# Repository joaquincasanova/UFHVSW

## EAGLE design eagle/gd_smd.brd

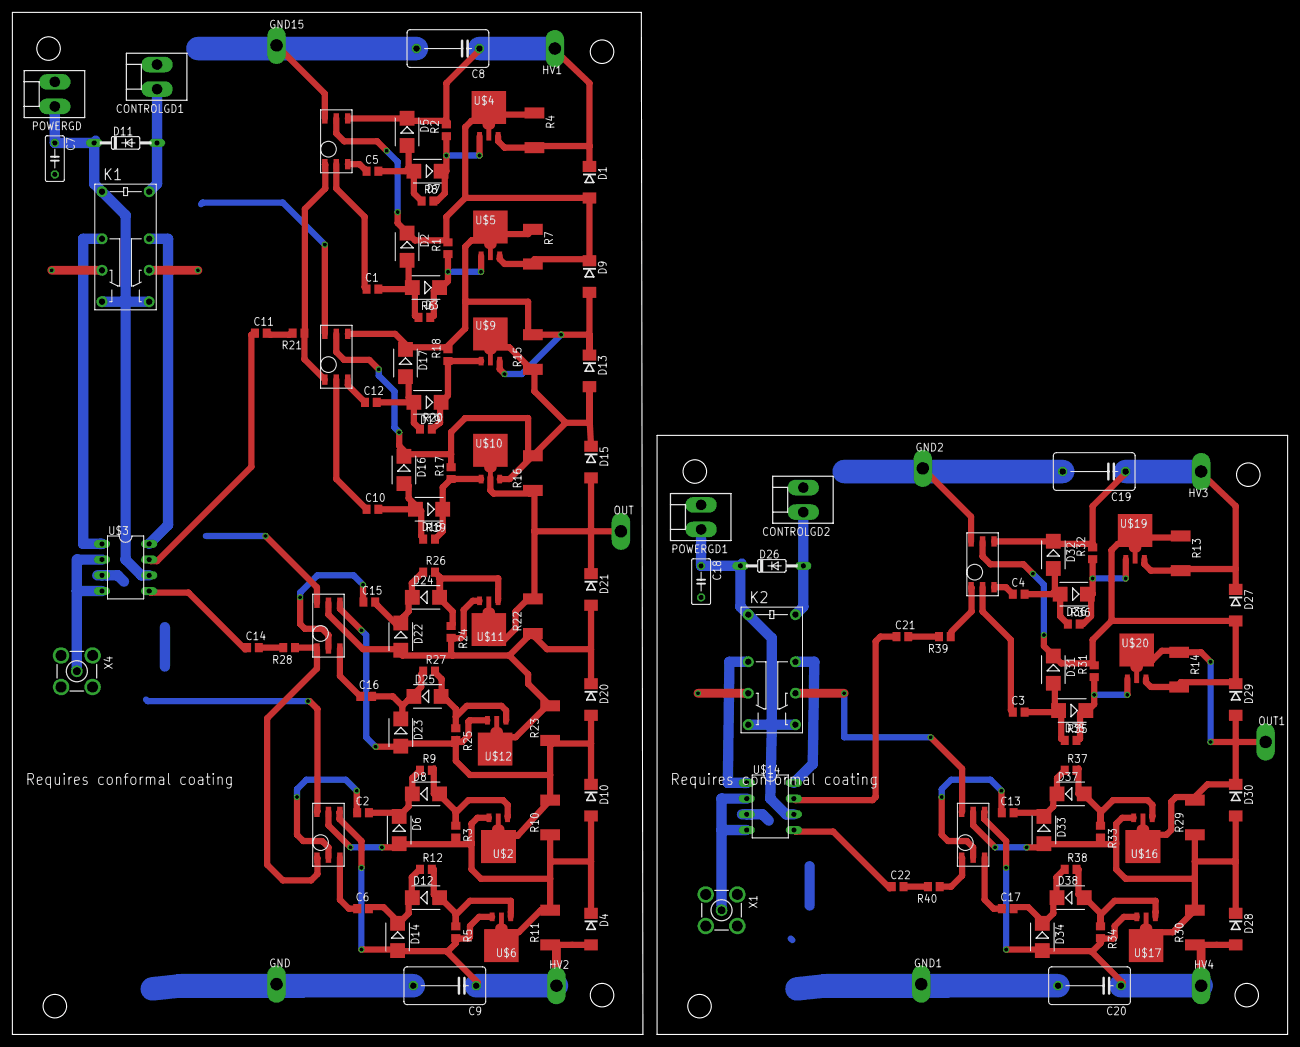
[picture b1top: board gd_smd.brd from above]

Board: 2 copper layers, 206.0 x 165.1 mm, 138 parts (0 on the bottom side), 74 nets.

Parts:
C1, C2, C3, C4, C5, C6, C10, C11, C12, C13, C14, C15, C16, C17, C21, C22: 1u; C0805
C7, C18: 10n; C050-030X075
C8, C9, C19, C20: 10p; C102-064X133
CONTROLGD1, CONTROLGD2: KK-156-2
D1, D4, D9, D10, D13, D15, D20, D21, D27, D28, D29, D30: SMBJ170D-M3/H; DO214AA
D2, D5, D6, D14, D16, D17, D22, D23, D31, D32, D33, D34: 1SMB5918BT3G; SMB
D3, D7, D8, D12, D18, D19, D24, D25, D35, D36, D37, D38: SMB
D11, D26: 1N4148DO35-10; DO35-10
GND, GND1, GND2, GND15: TPPAD1-20Y; P1-20Y
HV1, HV2, HV3, HV4: TPPAD1-20Y; P1-20Y
K1, K2: G5V-2
OUT, OUT1: TPPAD1-20Y; P1-20Y
POWERGD, POWERGD1: KK-156-2
R1, R2, R3, R5, R17, R18, R24, R25, R31, R32, R33, R34: 100k; R0805
R4, R7, R10, R11, R13, R14, R15, R16, R22, R23, R29, R30: 10M; R2512
R6, R8, R9, R12, R19, R20, R21, R26, R27, R28, R35, R36, R37, R38, R39, R40: 10; R0805
U$1, U$7, U$8, U$13, U$15, U$18: DA-2320SMD6; SMD6
U$2, U$6, U$11, U$12, U$16, U$17: VN2450; SOT89-BCE
U$3, U$14: UCC27425; DIL08
U$4, U$5, U$9, U$10, U$19, U$20: VP2450; SOT89-BCE
X1, X4: BU-SMA-V

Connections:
+15V: C7.1, D11.C, K1.1, K1.8, K1.9, POWERGD.1, U$3.6
+15V1: C18.1, D26.C, K2.1, K2.8, K2.9, POWERGD1.1, U$14.6
ENSW: CONTROLGD1.1, D11.A, K1.16
ENSW1: CONTROLGD2.1, D26.A, K2.16
GND: C7.2, C8.2, C9.2, CONTROLGD1.2, GND.TP, GND15.TP, K1.6, K1.11, POWERGD.2, U$1.P$6, U$3.3, U$7.P$6, U$8.P$6, U$13.P$6, X4.2, X4.3, X4.4, X4.5
GND1: C18.2, C19.2, C20.2, CONTROLGD2.2, GND1.TP, GND2.TP, K2.6, K2.11, POWERGD1.2, U$14.3, U$15.P$6, U$18.P$6, X1.2, X1.3, X1.4, X1.5
unnamed: U$3.2, U$3.4, X4.1
unnamed: C11.1, U$3.7
unnamed: U$14.2, U$14.4, X1.1
unnamed: C14.1, U$3.5
unnamed: C1.1, U$1.P$2
unnamed: C21.1, U$14.7
unnamed: C5.1, U$1.P$3
unnamed: D3.C, R1.1, R6.2, U$5.B
unnamed: C22.1, U$14.5
unnamed: C1.2, D2.A, D3.A, R6.1
unnamed: D12.A, R5.1, R12.2, U$6.B
unnamed: D7.C, R2.1, R8.2, U$4.B
unnamed: D4.C, D6.A, D10.A, R3.2, R10.1, R11.2, U$2.E, U$6.C, U$6.C@1, U$7.P$5
unnamed: K1.4, U$3.1
unnamed: K1.13, U$3.8
unnamed: C5.2, D5.A, D7.A, R8.1
unnamed: C8.1, D1.C, D5.C, HV1.TP, R2.2, R4.2, U$1.P$4, U$4.E
unnamed: D1.A, D2.C, D9.C, R1.2, R4.1, R7.2, U$1.P$5, U$4.C, U$4.C@1, U$5.E
unnamed: K2.4, U$14.1
unnamed: K2.13, U$14.8
unnamed: C3.1, U$15.P$2
unnamed: C2.1, U$7.P$2
unnamed: C6.1, U$7.P$3
unnamed: C9.1, D4.A, D14.A, HV2.TP, R5.2, R11.1, U$6.E, U$7.P$4
unnamed: C2.2, D6.C, D8.C, R9.1
unnamed: D15.A, D21.C, OUT.TP, R16.1, R22.2, U$10.C, U$10.C@1, U$11.C, U$11.C@1
unnamed: C6.2, D12.C, D14.C, R12.1
unnamed: C10.1, U$8.P$2
unnamed: C12.1, U$8.P$3
unnamed: C12.2, D17.A, D19.A, R20.1
unnamed: C4.1, U$15.P$3
unnamed: D9.A, D13.C, D17.C, R7.1, R15.2, R18.2, U$5.C, U$5.C@1, U$8.P$4, U$9.E
unnamed: D13.A, D15.C, D16.C, R15.1, R16.2, R17.2, U$8.P$5, U$9.C, U$9.C@1, U$10.E
unnamed: D18.C, R17.1, R19.2, U$10.B
unnamed: C10.2, D16.A, D18.A, R19.1
unnamed: D19.C, R18.1, R20.2, U$9.B
unnamed: R21.1, U$1.P$1, U$8.P$1
unnamed: C11.2, R21.2
unnamed: C13.1, U$18.P$2
unnamed: C15.1, U$13.P$2
unnamed: C16.1, U$13.P$3
unnamed: C15.2, D22.C, D24.C, R26.1
unnamed: C16.2, D23.C, D25.C, R27.1
unnamed: C17.1, U$18.P$3
unnamed: C13.2, D33.C, D37.C, R37.1
unnamed: D20.C, D21.A, D22.A, R22.1, R23.2, R24.2, U$11.E, U$12.C, U$12.C@1, U$13.P$5
unnamed: D25.A, R25.1, R27.2, U$12.B
unnamed: R28.1, U$7.P$1, U$13.P$1
unnamed: C14.2, R28.2
unnamed: D24.A, R24.1, R26.2, U$11.B
unnamed: D10.C, D20.A, D23.A, R10.2, R23.1, R25.2, U$2.C, U$2.C@1, U$12.E, U$13.P$4
unnamed: C17.2, D34.C, D38.C, R38.1
unnamed: C4.2, D32.A, D36.A, R36.1
unnamed: C19.1, D27.C, D32.C, HV3.TP, R13.2, R32.2, U$15.P$4, U$19.E
unnamed: D28.C, D30.A, D33.A, R29.1, R30.2, R33.2, U$16.E, U$17.C, U$17.C@1, U$18.P$5
unnamed: D27.A, D29.C, D31.C, R13.1, R14.2, R31.2, U$15.P$5, U$19.C, U$19.C@1, U$20.E
unnamed: D35.C, R31.1, R35.2, U$20.B
unnamed: C3.2, D31.A, D35.A, R35.1
unnamed: D38.A, R34.1, R38.2, U$17.B
unnamed: D36.C, R32.1, R36.2, U$19.B
unnamed: D37.A, R33.1, R37.2, U$16.B
unnamed: C20.1, D28.A, D34.A, HV4.TP, R30.1, R34.2, U$17.E, U$18.P$4
unnamed: R39.1, U$15.P$1
unnamed: C21.2, R39.2
unnamed: R40.1, U$18.P$1
unnamed: C22.2, R40.2
unnamed: D29.A, D30.C, OUT1.TP, R14.1, R29.2, U$16.C, U$16.C@1, U$20.C, U$20.C@1
unnamed: D8.A, R3.1, R9.2, U$2.B

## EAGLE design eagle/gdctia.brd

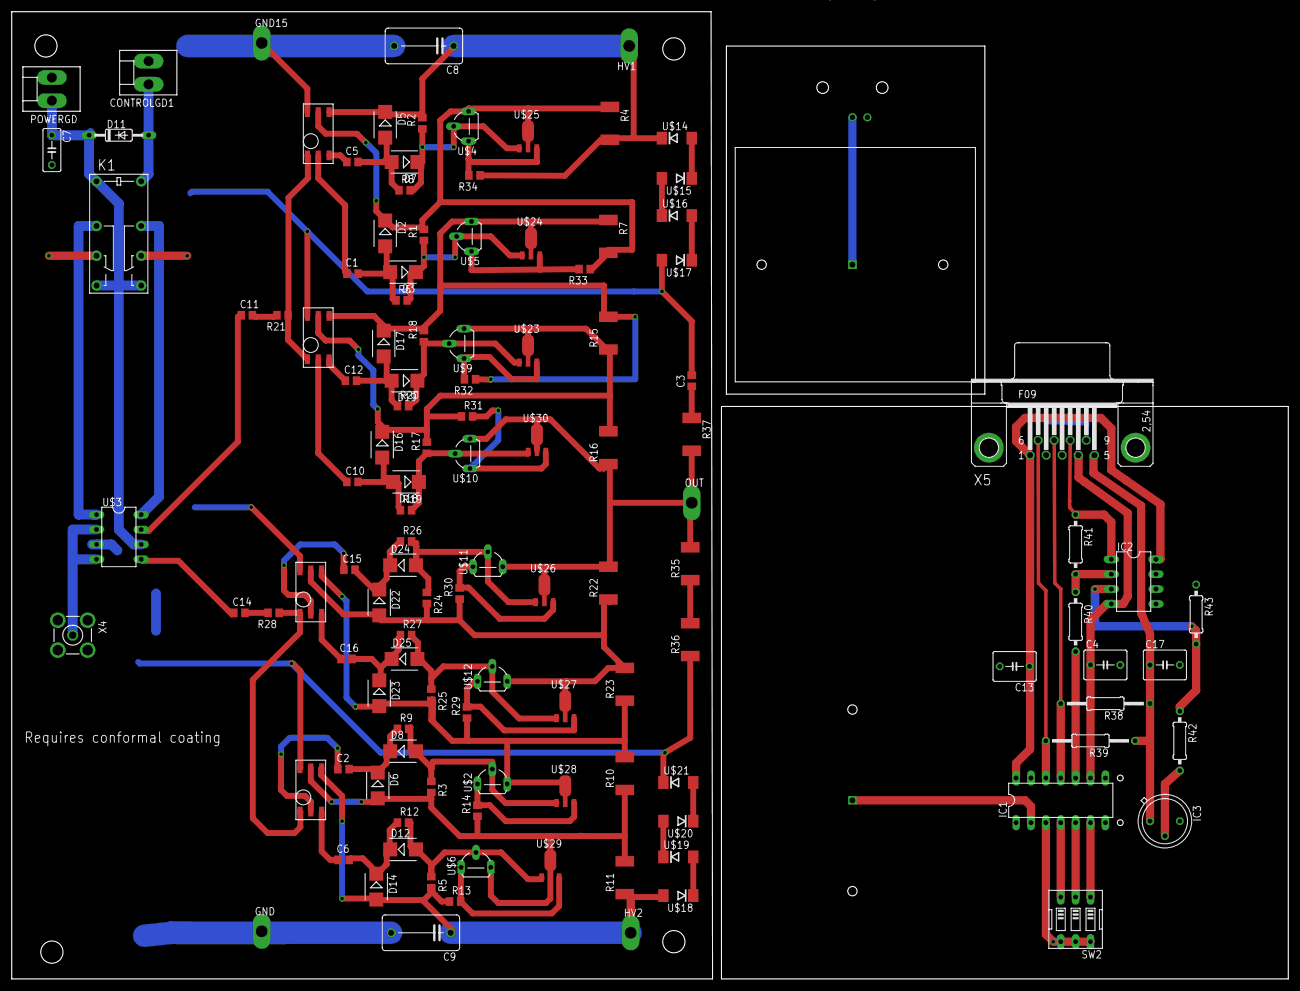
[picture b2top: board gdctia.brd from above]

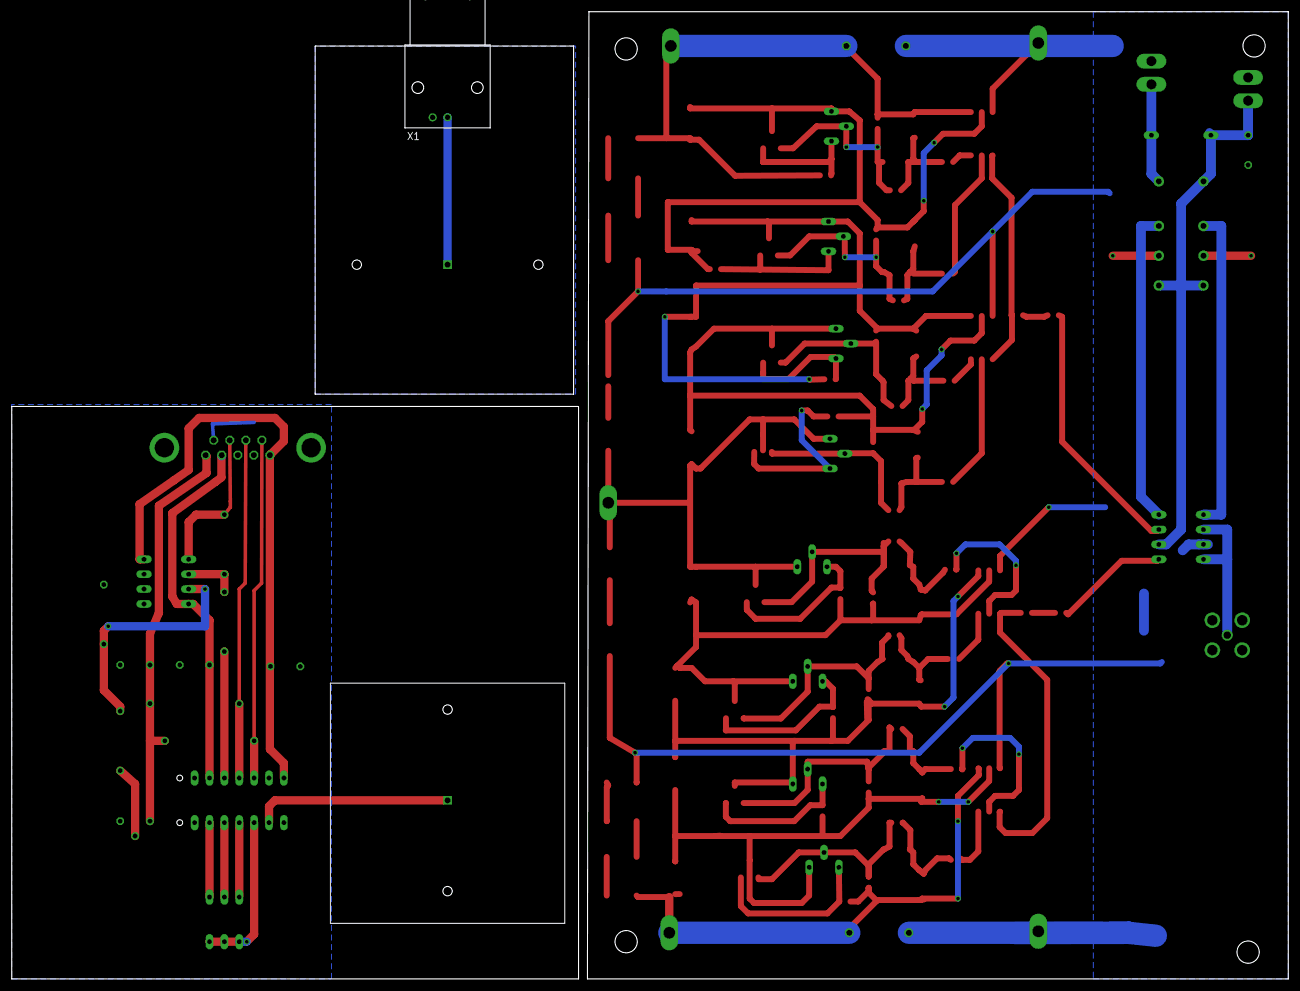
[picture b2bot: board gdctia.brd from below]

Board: 2 copper layers, 217.9 x 165.1 mm, 123 parts (2 on the bottom side), 78 nets.

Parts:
C1, C2, C5, C6, C10, C11, C12, C14, C15, C16: 1u; C0805
C3: 10n; C0805
C4, C13, C17: 10n; C050-050X075
C7: 10n; C050-030X075
C8, C9: 10p; C102-064X133
CONTROLGD1: KK-156-2
D2, D5, D6, D14, D16, D17, D22, D23: 1SMB5918BT3G; SMB
D3, D7, D8, D12, D18, D19, D24, D25: SMB
D11: 1N4148DO35-10; DO35-10
GND, GND15: TPPAD1-20Y; P1-20Y
HV1, HV2: TPPAD1-20Y; P1-20Y
IC1: IVC102UADAPTOR; DIL14
IC2: LT1352PA; DIL08
IC3: AD580H; TO39
K1: G5V-2
OUT: TPPAD1-20Y; P1-20Y
POWERGD: KK-156-2
R1, R2, R3, R5, R17, R18, R24, R25: 100k; R0805
R4, R7, R10, R11, R15, R16, R22, R23, R35, R36, R37: 10M; R2512
R6, R8, R9, R12, R19, R20, R21, R26, R27, R28: 10; R0805
R13, R14, R29, R30: 6.67; R0805
R31, R32, R33, R34: 1.25; R0805
R38, R39: 10k; 0207/15
R40, R43: 10k; 0207/10
R41, R42: 1.5M; 0207/10
SW2: EDG-03
U$1, U$7, U$8, U$13: DA-2320SMD6; SMD6
U$2, U$6, U$11, U$12: VN0550L; TO92L
U$3: UCC27425; DIL08
U$4, U$5, U$9, U$10: VP0550L; TO92L
U$14, U$15, U$16, U$17, U$18, U$19, U$20, U$21: SMBJ170D-M3/H; DO214AA
U$22, U$31: CTIA
U$23, U$24, U$25, U$30: VP2450; SOT89-BCE
U$26, U$27, U$28, U$29: VN2450; SOT89-BCE
X1: 1-227161-0; AMP_227161
X4: BU-SMA-V
X5: F09HP

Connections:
+5V: C17.1, IC3.1, R38.1, R39.1, X5.5
+15V: C7.1, D11.C, K1.1, K1.8, K1.9, POWERGD.1, U$3.6
+15V1: C13.1, IC1.14, IC2.8, X5.1
-15V: C4.1, IC1.9, IC2.4, X5.4
ENSW: CONTROLGD1.1, D11.A, K1.16
GND: C3.2, C7.2, C8.2, C9.2, CONTROLGD1.2, GND.TP, GND15.TP, K1.6, K1.11, POWERGD.2, R36.1, U$1.P$6, U$3.3, U$7.P$6, U$8.P$6, U$13.P$6, U$17.A, U$21.C, X4.2, X4.3, X4.4, X4.5
GND1: C4.2, C17.2, IC1.1, IC1.13, IC3.3, R43.1, X5.2, X5.3, X5.9
unnamed: U$3.2, U$3.4, X4.1
unnamed: C11.1, U$3.7
unnamed: R13.2, U$6.3, U$29.E
unnamed: C14.1, U$3.5
unnamed: C1.1, U$1.P$2
unnamed: R14.2, U$2.3, U$28.E
unnamed: C5.1, U$1.P$3
unnamed: D3.C, R1.1, R6.2, U$5.2, U$24.B
unnamed: R29.2, U$12.3, U$27.E
unnamed: C1.2, D2.A, D3.A, R6.1
unnamed: D12.A, R5.1, R12.2, U$6.2, U$29.B
unnamed: D7.C, R2.1, R8.2, U$4.2, U$25.B
unnamed: D6.A, R3.2, R10.1, R11.2, R14.1, U$6.1, U$7.P$5, U$29.C, U$29.C@1
unnamed: K1.4, U$3.1
unnamed: K1.13, U$3.8
unnamed: C5.2, D5.A, D7.A, R8.1
unnamed: C8.1, D5.C, HV1.TP, R2.2, R4.2, R34.1, U$1.P$4, U$14.C
unnamed: D2.C, R1.2, R4.1, R7.2, R33.1, U$1.P$5, U$4.1, U$25.C, U$25.C@1
unnamed: R30.2, U$11.3, U$26.E
unnamed: R34.2, U$4.3, U$25.E
unnamed: R33.2, U$5.3, U$24.E
unnamed: C2.1, U$7.P$2
unnamed: C6.1, U$7.P$3
unnamed: C9.1, D14.A, HV2.TP, R5.2, R11.1, R13.1, U$7.P$4, U$18.A
unnamed: C2.2, D6.C, D8.C, R9.1
unnamed: OUT.TP, R16.1, R22.2, R35.2, R37.2, U$10.1, U$11.1, U$26.C, U$26.C@1, U$30.C, U$30.C@1
unnamed: C6.2, D12.C, D14.C, R12.1
unnamed: C10.1, U$8.P$2
unnamed: C12.1, U$8.P$3
unnamed: C12.2, D17.A, D19.A, R20.1
unnamed: R31.2, U$10.3, U$30.E
unnamed: D17.C, R7.1, R15.2, R18.2, R32.1, U$5.1, U$8.P$4, U$24.C, U$24.C@1
unnamed: D16.C, R15.1, R16.2, R17.2, R31.1, U$8.P$5, U$9.1, U$23.C, U$23.C@1
unnamed: D18.C, R17.1, R19.2, U$10.2, U$30.B
unnamed: C10.2, D16.A, D18.A, R19.1
unnamed: D19.C, R18.1, R20.2, U$9.2, U$23.B
unnamed: R21.1, U$1.P$1, U$8.P$1
unnamed: C11.2, R21.2
unnamed: R32.2, U$9.3, U$23.E
unnamed: C15.1, U$13.P$2
unnamed: C16.1, U$13.P$3
unnamed: C15.2, D22.C, D24.C, R26.1
unnamed: C16.2, D23.C, D25.C, R27.1
unnamed: R35.1, R36.2
unnamed: C3.1, R37.1
unnamed: D22.A, R22.1, R23.2, R24.2, R30.1, U$12.1, U$13.P$5, U$27.C, U$27.C@1
unnamed: D25.A, R25.1, R27.2, U$12.2, U$27.B
unnamed: R28.1, U$7.P$1, U$13.P$1
unnamed: C14.2, R28.2
unnamed: D24.A, R24.1, R26.2, U$11.2, U$26.B
unnamed: D23.A, R10.2, R23.1, R25.2, R29.1, U$2.1, U$13.P$4, U$28.C, U$28.C@1
unnamed: U$14.A, U$15.C
unnamed: U$15.A, U$16.C
unnamed: U$16.A, U$17.C
unnamed: U$18.C, U$19.A
unnamed: U$19.C, U$20.A
unnamed: U$20.C, U$21.A
unnamed: IC1.6, SW2.1
unnamed: IC1.5, SW2.2
unnamed: IC1.4, SW2.3
unnamed: IC1.3, SW2.4, SW2.5, SW2.6
unnamed: IC1.10, R40.2
unnamed: IC2.2, R40.1, R41.2
unnamed: IC2.3, R42.1, R43.2
unnamed: IC3.2, R42.2
unnamed: U$31.P$1, X1.1
unnamed: D8.A, R3.1, R9.2, U$2.2, U$28.B
RESET: IC1.12, R39.2, X5.6
SAMPLE: IC1.11, R38.2, X5.7
VIN: IC1.2, U$22.P$1
VOUT: IC2.1, R41.1, X5.8

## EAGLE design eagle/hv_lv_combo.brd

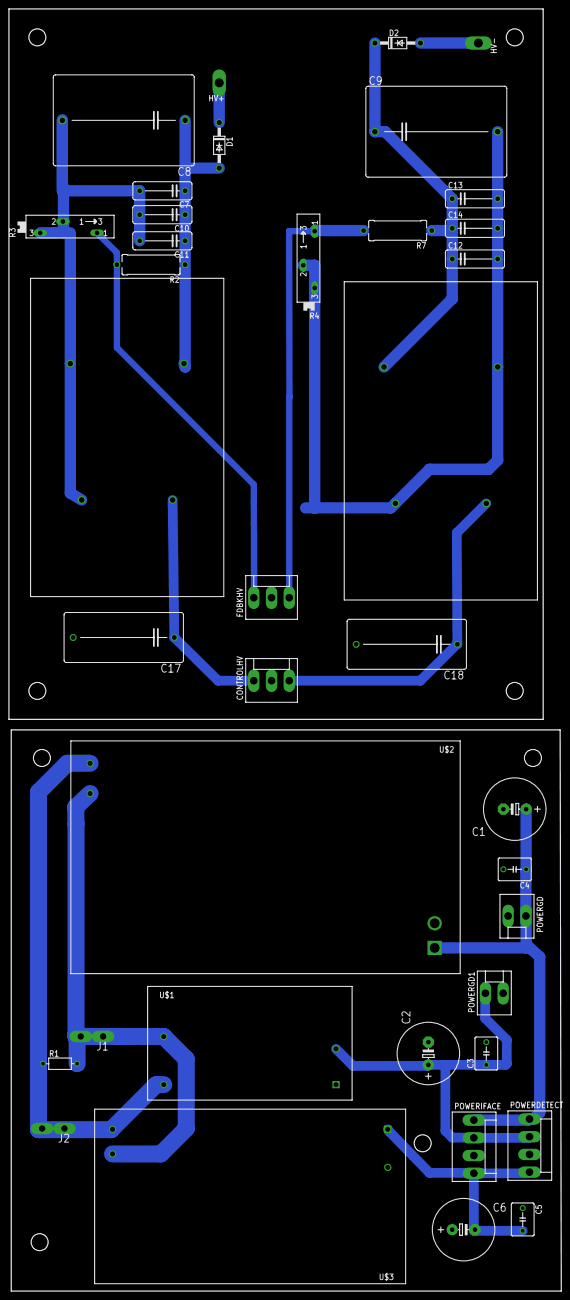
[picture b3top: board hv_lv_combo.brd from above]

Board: 2 copper layers, 123.4 x 286.5 mm, 38 parts (0 on the bottom side), 15 nets.

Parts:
C1, C2, C6: E5-13
C3, C4, C5: C050-050X075
C7, C12: .01u; C102-043X133
C8, C9: 1u; C275-205X316
C10, C13: 1n; C102-043X133
C11, C14: 10p; C102-043X133
C17, C18: .1u; C225-113X268
CONTROLHV: KK-156-3
D1, D2: 1N4004; DO41-10
FDBKHV: KK-156-3
HV+: TPPAD1-20Y; P1-20Y
HV-: TPPAD1-20Y; P1-20Y
J1, J2: PIN2F061.100; F061.100
POWERDETECT: KK-156-4
POWERGD, POWERGD1: KK-156-2
POWERIFACE: KK-156-4
R1: VARISTOR-7,5; R-7,5
R2, R7: 2M; P0613/15
R3, R4: SP19L
U$1: IRM-05-05
U$2: IRM-60-12
U$3: IRM-30-15
U$4, U$5: EMCO-F104PIN; EMCO-F

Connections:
+15V: C1.+, C4.1, POWERDETECT.1, POWERGD.1, POWERIFACE.1, U$2.P$1
-15V: C5.2, C6.-, POWERDETECT.4, POWERIFACE.4, U$3.-V
GND: C1.-, C2.-, C3.2, C4.2, C5.1, C6.+, POWERDETECT.3, POWERGD.2, POWERGD1.2, POWERIFACE.3, U$1.-V, U$2.P$2, U$3.+V
GND1: C7.2, C8.2, C9.2, C10.2, C11.2, C12.2, C13.2, C14.2, C17.2, C18.2, CONTROLHV.2, FDBKHV.2, R3.E, R3.S, R4.E, R4.S, U$4.P$2, U$4.P$4, U$5.P$2, U$5.P$3
unnamed: J1.A1, J1.A2, R1.2, U$1.ACN, U$2.P$4, U$3.ACN
unnamed: J2.A1, J2.A2, R1.1, U$1.ACL, U$2.P$3, U$3.ACL
unnamed: C7.1, C8.1, C10.1, C11.1, D1.A, R2.1, U$4.P$3
unnamed: C9.1, C12.1, C13.1, C14.1, D2.C, R7.1, U$5.P$4
unnamed: FDBKHV.1, R2.2, R3.A
unnamed: D1.C, HV+.TP
unnamed: FDBKHV.3, R4.A, R7.2
unnamed: D2.A, HV-.TP
unnamed: C17.1, CONTROLHV.1, U$4.P$1
unnamed: C18.1, CONTROLHV.3, U$5.P$1
VCC: C2.+, C3.1, POWERDETECT.2, POWERGD1.1, POWERIFACE.2, U$1.+V

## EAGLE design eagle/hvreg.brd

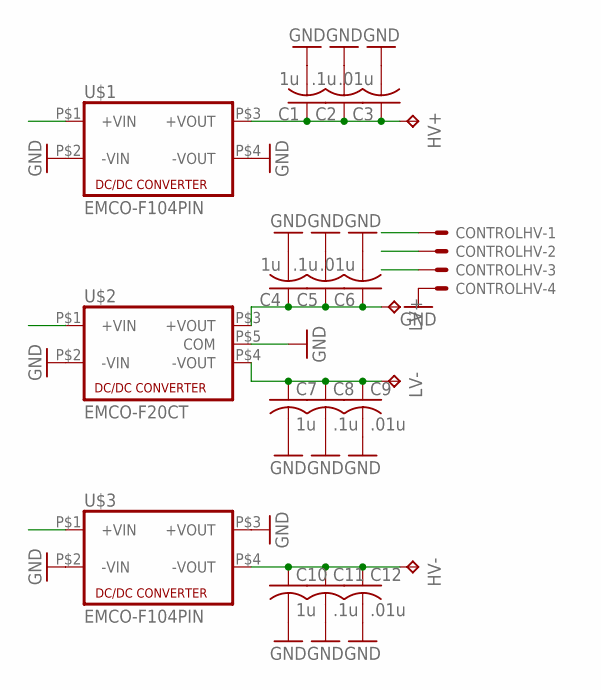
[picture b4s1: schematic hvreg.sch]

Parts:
C1, C4, C7, C10: 1u; C275-113X316
C2, C5, C8, C11: .1u; C102-043X133
C3, C6, C9, C12: .01u; C075-042X103
CONTROLHV: KK-156-4
HV+: TPPAD1-20Y; P1-20Y
HV-: TPPAD1-20Y; P1-20Y
LV+: TPPAD1-20Y; P1-20Y
LV-: TPPAD1-20Y; P1-20Y
U$1, U$3: EMCO-F104PIN; EMCO-F
U$2: EMCO-F20CT; EMCO-F*CT

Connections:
GND: C1.2, C2.2, C3.2, C4.2, C5.2, C6.2, C7.2, C8.2, C9.2, C10.2, C11.2, C12.2, CONTROLHV.4, U$1.P$2 (-VIN), U$1.P$4 (-VOUT), U$2.P$2 (-VIN), U$2.P$5 (COM), U$3.P$2 (-VIN), U$3.P$3 (+VOUT)
unnamed: C1.1, C2.1, C3.1, HV+.TP, U$1.P$3 (+VOUT)
unnamed: C10.1, C11.1, C12.1, HV-.TP, U$3.P$4 (-VOUT)
unnamed: C4.1, C5.1, C6.1, LV+.TP, U$2.P$3 (+VOUT)
unnamed: C7.1, C8.1, C9.1, LV-.TP, U$2.P$4 (-VOUT)
VREG1: CONTROLHV.1, U$1.P$1 (+VIN)
VREG2: CONTROLHV.2, U$2.P$1 (+VIN)
VREG3: CONTROLHV.3, U$3.P$1 (+VIN)

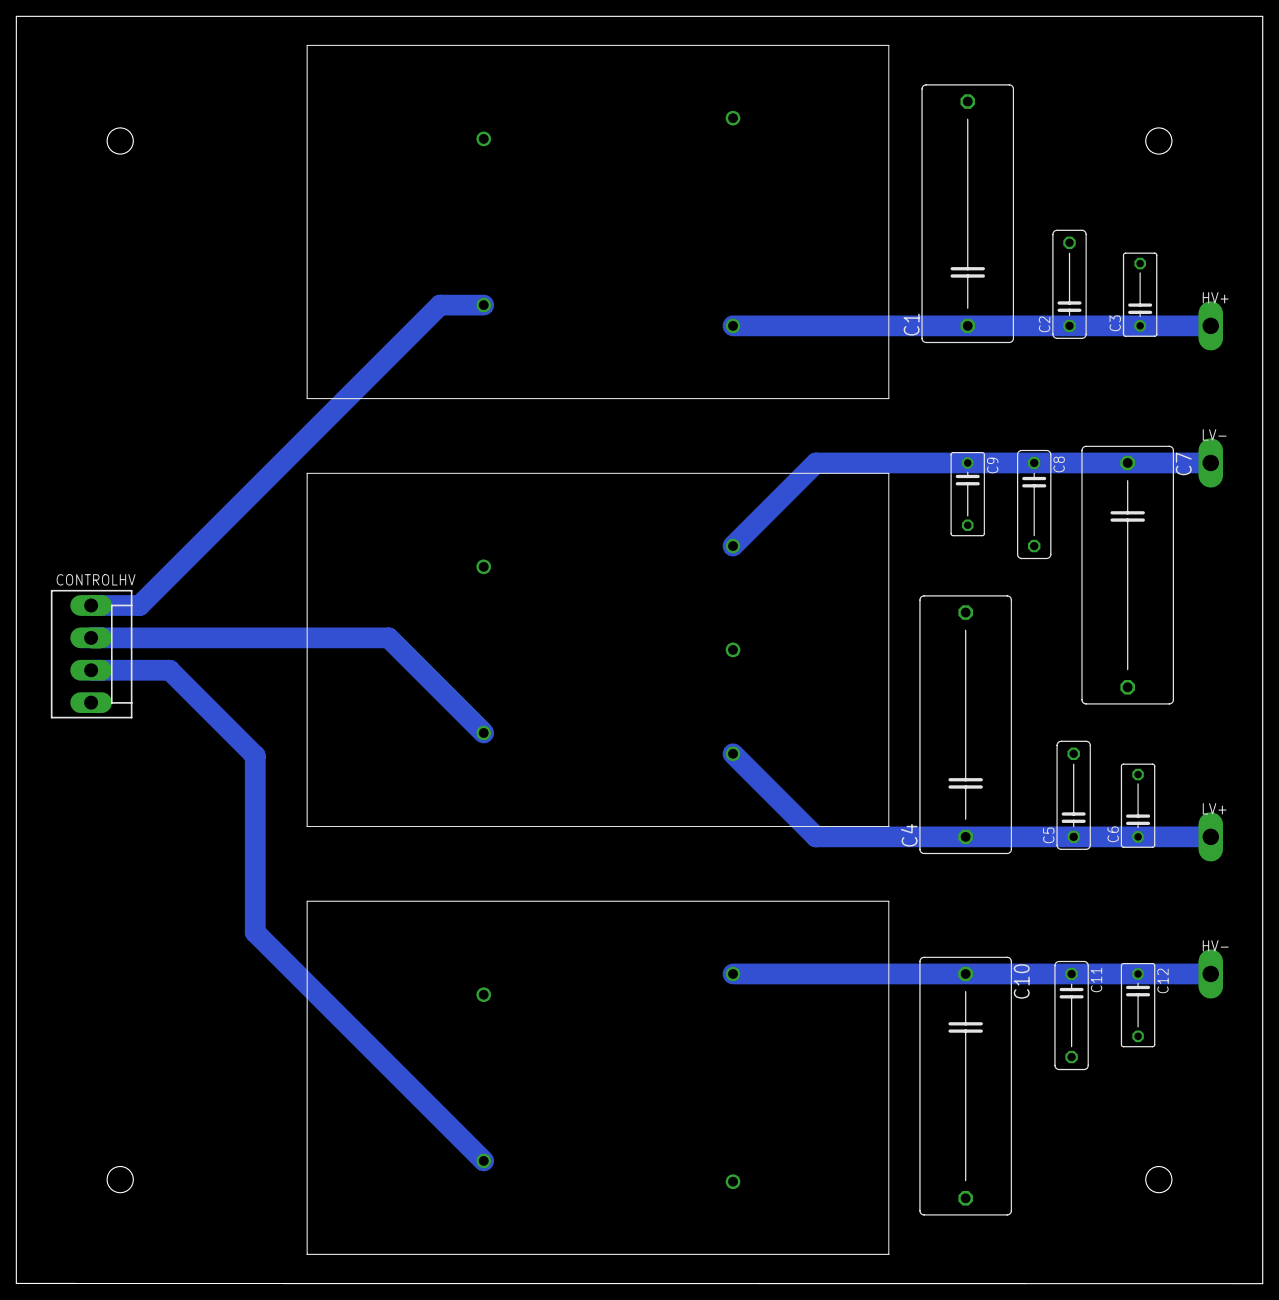
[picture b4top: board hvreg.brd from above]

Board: 2 copper layers, 152.4 x 155.0 mm, 20 parts (0 on the bottom side), 8 nets.

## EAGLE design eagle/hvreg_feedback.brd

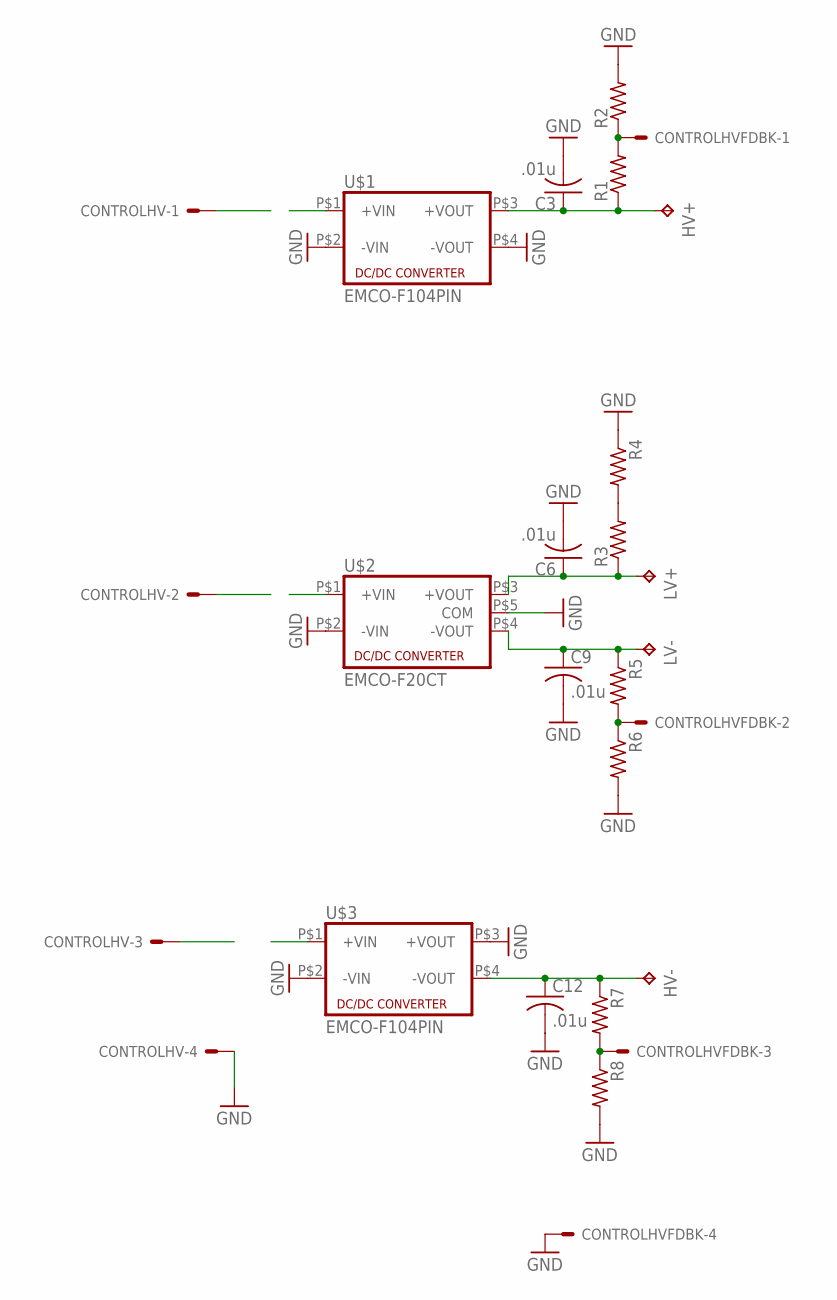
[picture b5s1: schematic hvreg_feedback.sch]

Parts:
C3, C6, C9, C12: .01u; C075-042X103
CONTROLHV: KK-156-4
CONTROLHVFDBK: KK-156-4
HV+: TPPAD1-20Y; P1-20Y
HV-: TPPAD1-20Y; P1-20Y
LV+: TPPAD1-20Y; P1-20Y
LV-: TPPAD1-20Y; P1-20Y
R1, R2, R3, R4, R5, R6, R7, R8: R-US_0207/12; 0207/12
U$1, U$3: EMCO-F104PIN; EMCO-F
U$2: EMCO-F20CT; EMCO-F*CT

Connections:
GND: C3.2, C6.2, C9.2, C12.2, CONTROLHV.4, CONTROLHVFDBK.4, R2.2, R4.1, R6.2, R8.2, U$1.P$2 (-VIN), U$1.P$4 (-VOUT), U$2.P$2 (-VIN), U$2.P$5 (COM), U$3.P$2 (-VIN), U$3.P$3 (+VOUT)
unnamed: C3.1, HV+.TP, R1.1, U$1.P$3 (+VOUT)
unnamed: C12.1, HV-.TP, R7.1, U$3.P$4 (-VOUT)
unnamed: CONTROLHVFDBK.1, R1.2, R2.1
unnamed: R3.2, R4.2
unnamed: C6.1, LV+.TP, R3.1, U$2.P$3 (+VOUT)
unnamed: C9.1, LV-.TP, R5.1, U$2.P$4 (-VOUT)
unnamed: CONTROLHVFDBK.2, R5.2, R6.1
unnamed: CONTROLHVFDBK.3, R7.2, R8.1
VREG1: CONTROLHV.1, U$1.P$1 (+VIN)
VREG2: CONTROLHV.2, U$2.P$1 (+VIN)
VREG3: CONTROLHV.3, U$3.P$1 (+VIN)

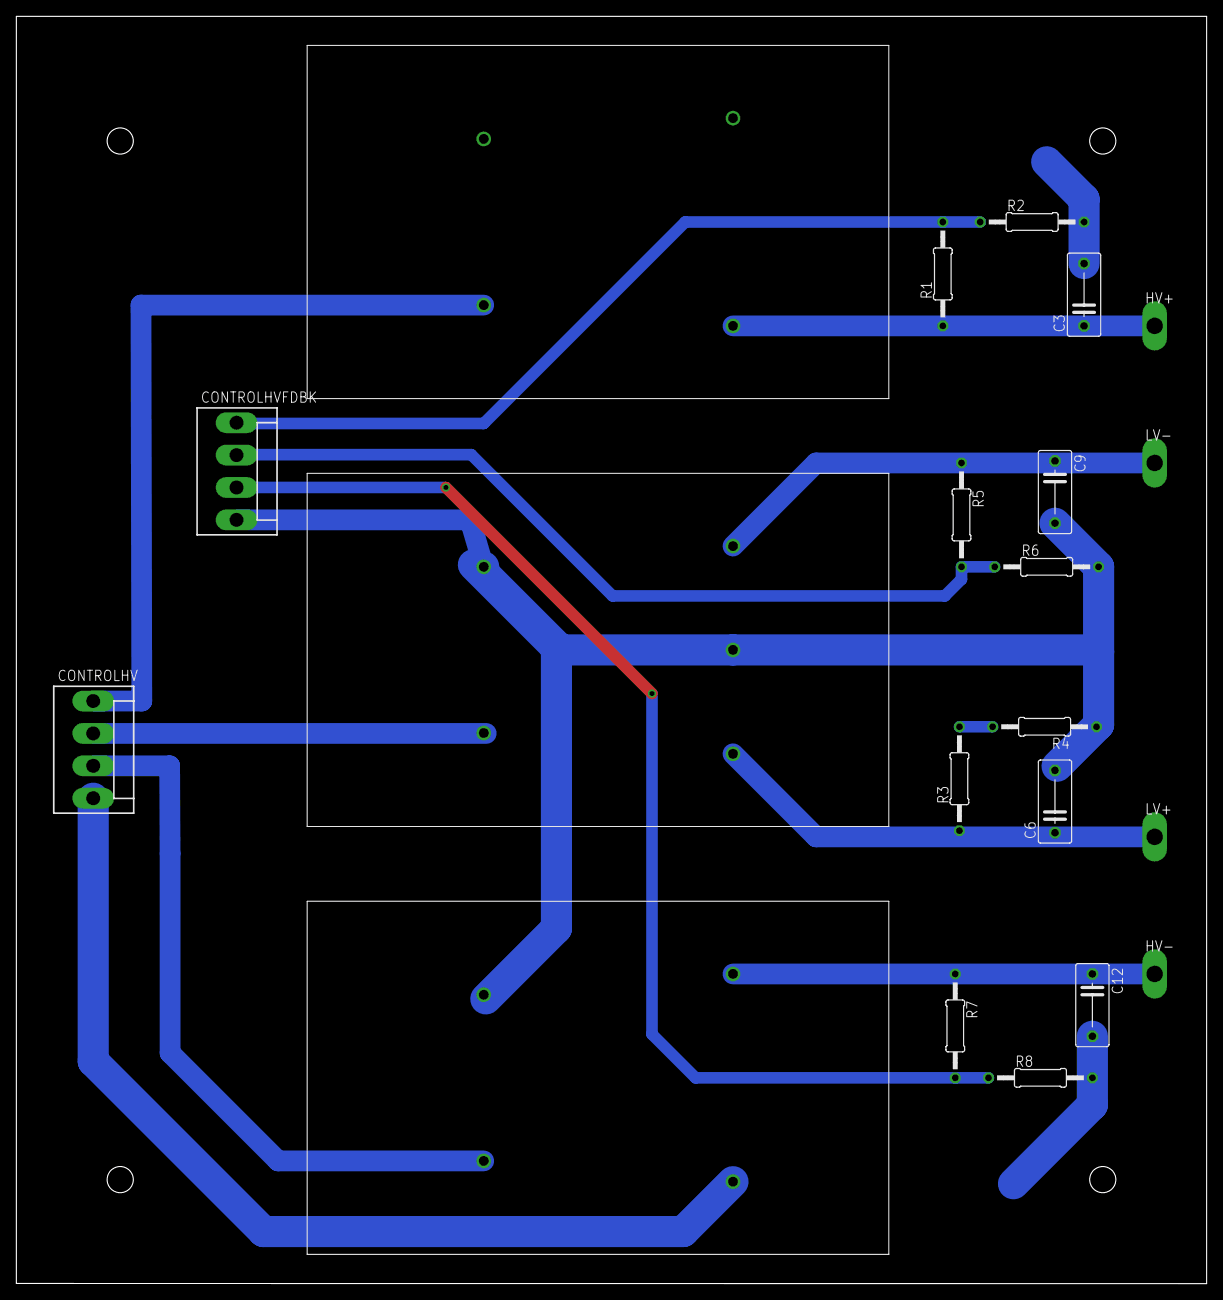
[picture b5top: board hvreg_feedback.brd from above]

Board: 2 copper layers, 145.5 x 155.0 mm, 21 parts (0 on the bottom side), 12 nets.

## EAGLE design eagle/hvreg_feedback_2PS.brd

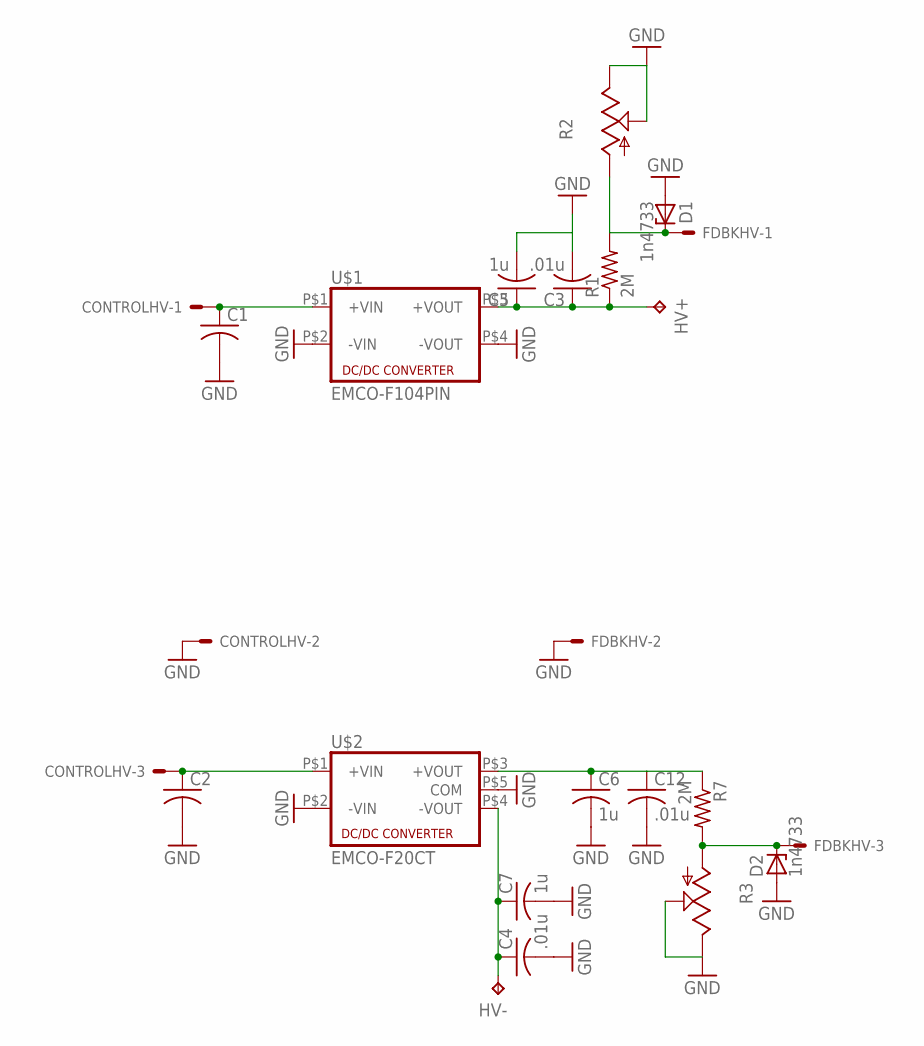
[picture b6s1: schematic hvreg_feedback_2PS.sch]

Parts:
C1, C2: C-US050-030X075; C050-030X075
C3, C4, C12: .01u; C075-042X103
C5, C6, C7: 1u; C225-108X268
CONTROLHV: KK-156-3
D1, D2: 1n4733; ZDIO-10
FDBKHV: KK-156-3
HV+: TPPAD1-20Y; P1-20Y
HV-: TPPAD1-20Y; P1-20Y
R1, R7: 2M; 0207/12
R2, R3: TRIM_US-B90P; SP19L
U$1: EMCO-F104PIN; EMCO-F
U$2: EMCO-F20CT; EMCO-F*CT

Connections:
GND: C1.2, C2.2, C3.2, C4.2, C5.2, C6.2, C7.2, C12.2, CONTROLHV.2, D1.A, D2.A, FDBKHV.2, R2.E, R2.S, R3.E, R3.S, U$1.P$2 (-VIN), U$1.P$4 (-VOUT), U$2.P$2 (-VIN), U$2.P$5 (COM)
unnamed: C3.1, C5.1, HV+.TP, R1.1, U$1.P$3 (+VOUT)
unnamed: C6.1, C12.1, R7.1, U$2.P$3 (+VOUT)
unnamed: D1.C, FDBKHV.1, R1.2, R2.A
unnamed: C1.1, CONTROLHV.1, U$1.P$1 (+VIN)
unnamed: C2.1, CONTROLHV.3, U$2.P$1 (+VIN)
unnamed: C4.1, C7.1, HV-.TP, U$2.P$4 (-VOUT)
unnamed: D2.C, FDBKHV.3, R3.A, R7.2

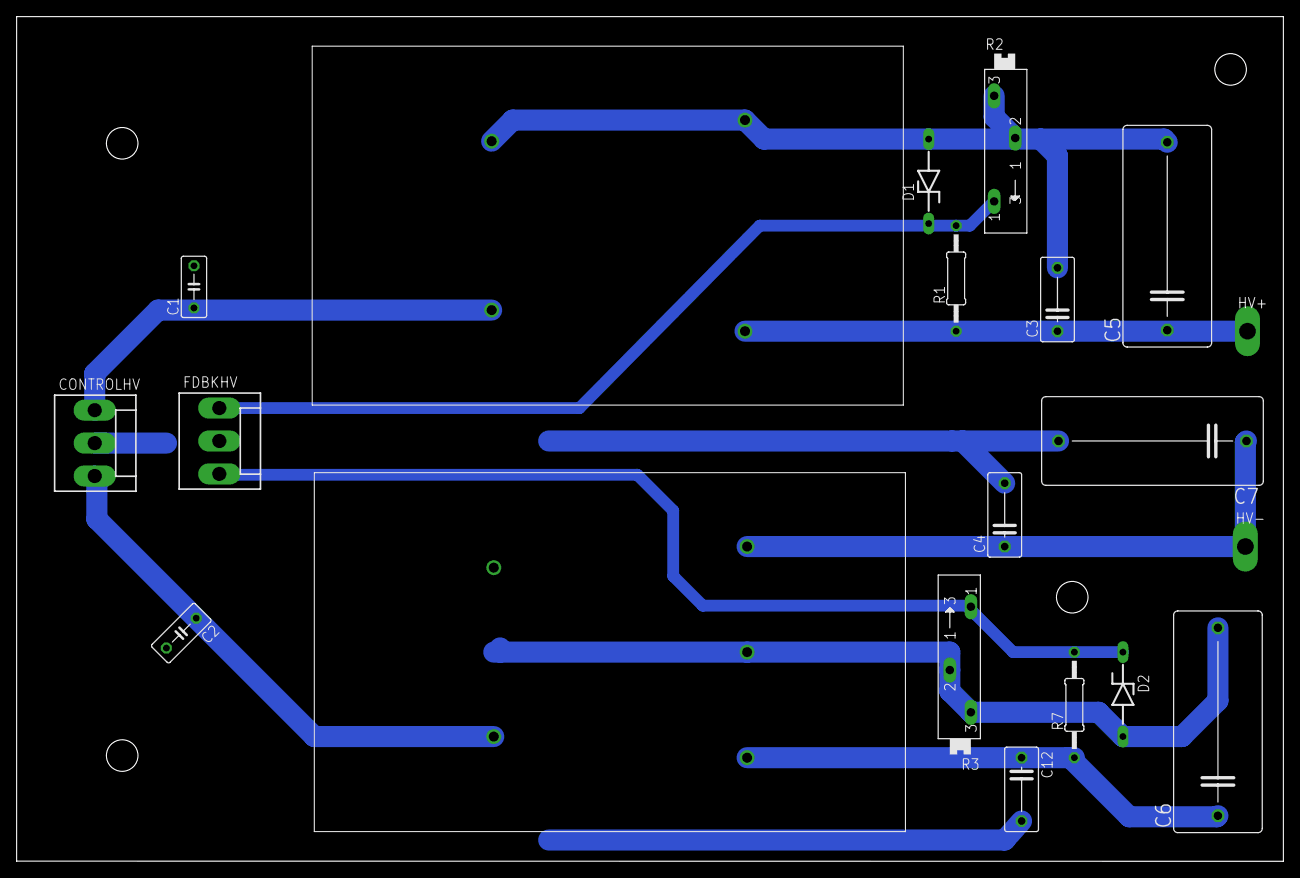
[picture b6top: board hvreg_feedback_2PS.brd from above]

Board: 2 copper layers, 152.4 x 101.6 mm, 20 parts (0 on the bottom side), 8 nets.

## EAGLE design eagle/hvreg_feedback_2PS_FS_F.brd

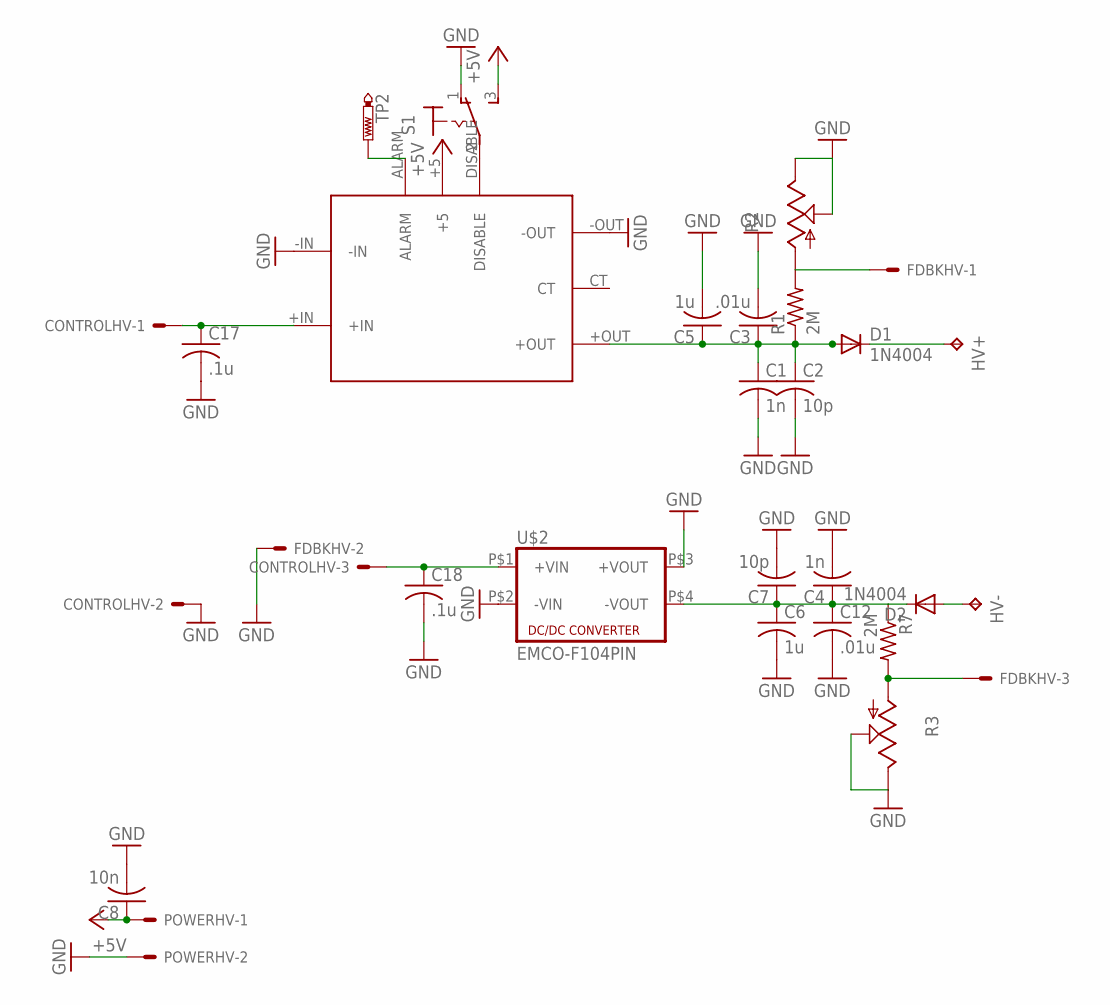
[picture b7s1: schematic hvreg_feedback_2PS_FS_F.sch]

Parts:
C1, C4: 1n; C102-043X133
C2, C7: 10p; C102-043X133
C3, C12: .01u; C102-043X133
C5, C6: 1u; C275-205X316
C8: 10n; C050-024X044
C17, C18: .1u; C225-113X268
CONTROLHV: KK-156-3
D1, D2: 1N4004; DO41-10
FDBKHV: KK-156-3
HV+: TPPAD1-20Y; P1-20Y
HV-: TPPAD1-20Y; P1-20Y
POWERHV: KK-156-2
R1, R7: 2M; P0613/15
R2, R3: TRIM_US-B90P; SP19L
S1: M9040P
TP2: PTR1PAD1-20Y; P1-20Y
U$1: EMCO-FS10; EMCO-FS
U$2: EMCO-F104PIN; EMCO-F

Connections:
+5V: C8.1, POWERHV.1, S1.3 (S), U$1.+5
GND: C1.2, C2.2, C3.2, C4.2, C5.2, C6.2, C7.2, C8.2, C12.2, C17.2, C18.2, CONTROLHV.2, FDBKHV.2, POWERHV.2, R2.E, R2.S, R3.E, R3.S, S1.1 (O), U$1.-IN, U$1.-OUT, U$2.P$2 (-VIN), U$2.P$3 (+VOUT)
unnamed: C1.1, C2.1, C3.1, C5.1, D1.A, R1.1, U$1.+OUT
unnamed: C4.1, C6.1, C7.1, C12.1, D2.C, R7.1, U$2.P$4 (-VOUT)
unnamed: FDBKHV.1, R1.2, R2.A
unnamed: D2.A, HV-.TP
unnamed: S1.2, U$1.DISABLE
unnamed: D1.C, HV+.TP
unnamed: FDBKHV.3, R3.A, R7.2
unnamed: TP2.TP, U$1.ALARM
unnamed: C17.1, CONTROLHV.1, U$1.+IN
unnamed: C18.1, CONTROLHV.3, U$2.P$1 (+VIN)

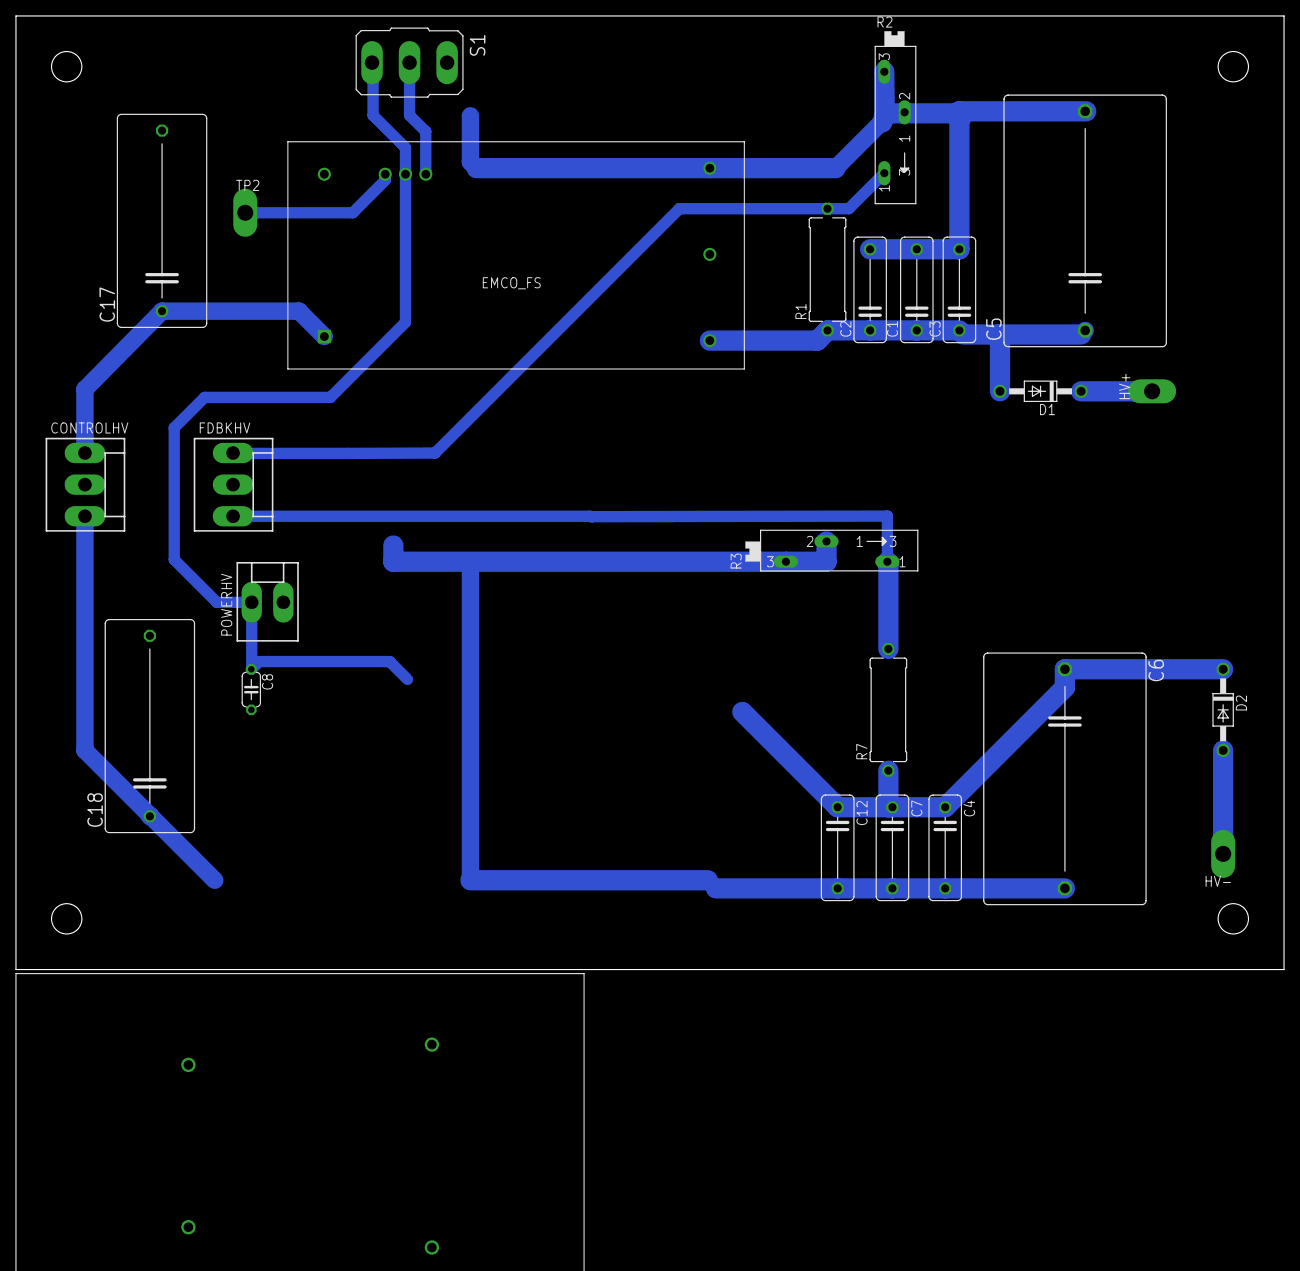
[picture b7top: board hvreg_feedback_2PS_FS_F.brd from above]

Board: 2 copper layers, 158.8 x 119.4 mm, 26 parts (0 on the bottom side), 12 nets.
